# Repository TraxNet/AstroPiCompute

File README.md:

# AstroPiCompute
Astronomy 12V PSU with raspberryPi connection

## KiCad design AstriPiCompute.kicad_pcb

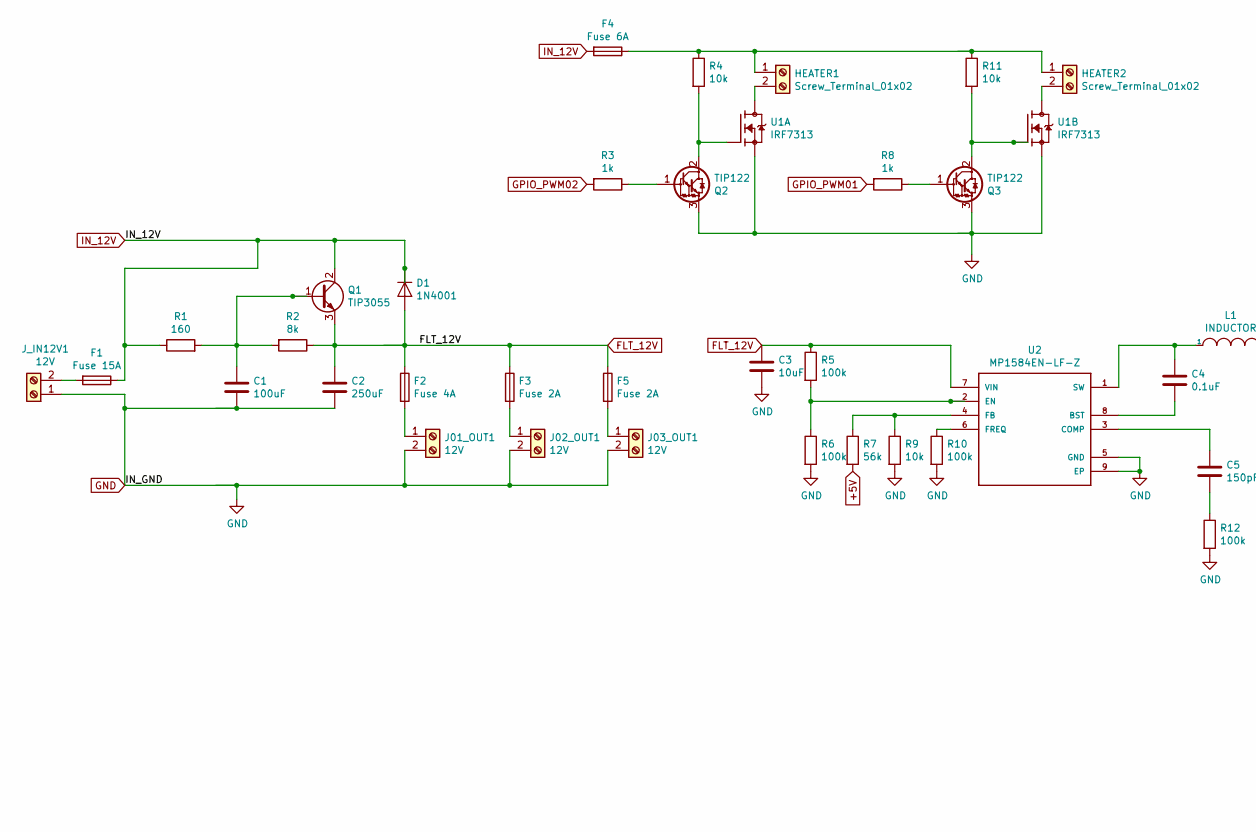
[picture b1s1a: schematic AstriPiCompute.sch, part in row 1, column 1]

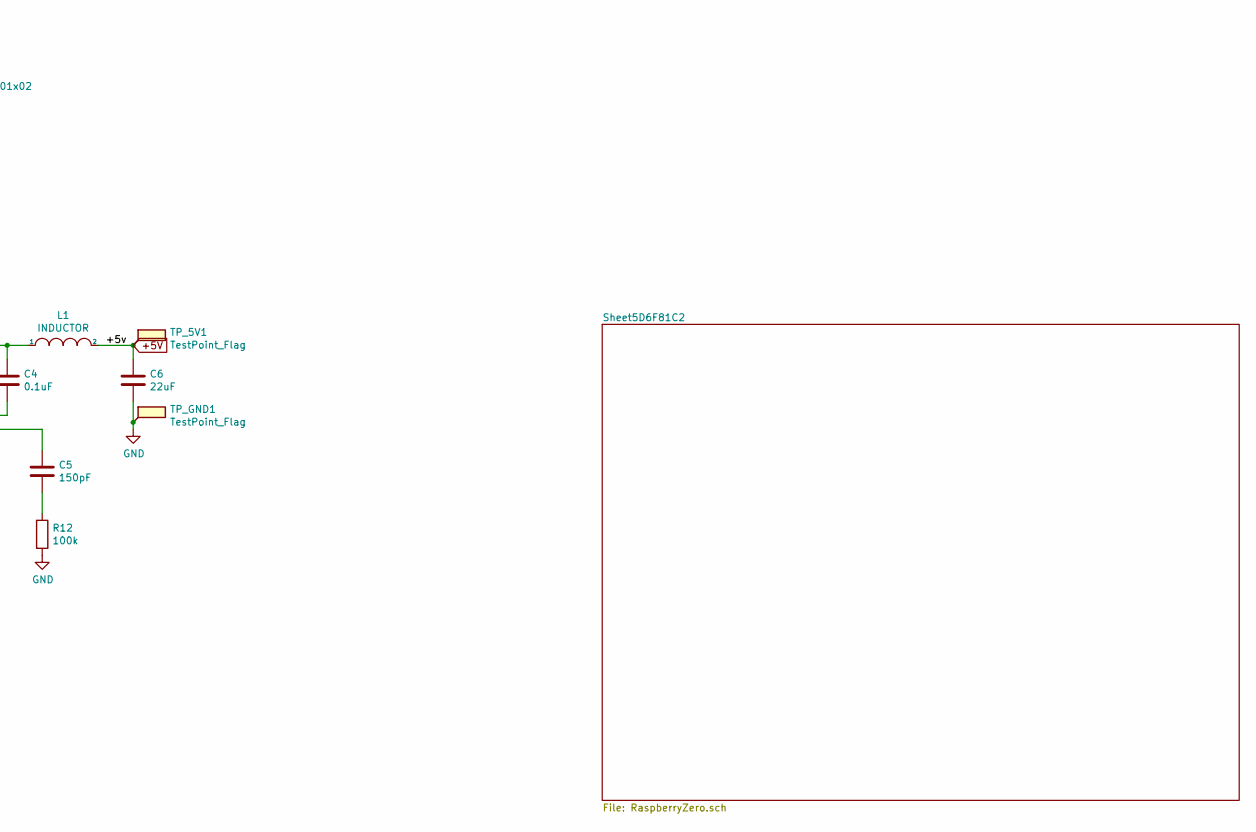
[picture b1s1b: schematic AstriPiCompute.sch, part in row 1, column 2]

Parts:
C1: 100uF; CP_Elec_5x5.4
C2: 250uF; CP_Elec_6.3x5.4
C3: 10uF; C_0805_2012Metric
C4: 0.1uF; C_0805_2012Metric
C5: 150pF; C_0805_2012Metric
C6: 22uF; C_0805_2012Metric
D1: 1N4001; D_0805_2012Metric_Pad1.15x1.40mm_HandSolder
F1: Fuse 15A; Fuse_1206_3216Metric_Pad1.42x1.75mm_HandSolder
F2: Fuse 4A; Fuse_1206_3216Metric_Pad1.42x1.75mm_HandSolder
F3, F5: Fuse 2A; Fuse_1206_3216Metric_Pad1.42x1.75mm_HandSolder
F4: Fuse 6A; Fuse_1206_3216Metric_Pad1.42x1.75mm_HandSolder
HEATER1, HEATER2: Screw_Terminal_01x02; SolderWirePad_1x02_P5.08mm_Drill1.5mm
J01_OUT1, J02_OUT1, J03_OUT1: 12V; SolderWirePad_1x02_P5.08mm_Drill1.5mm
J_IN12V1: 12V; SolderWirePad_1x02_P5.08mm_Drill1.5mm
L1: INDUCTOR; L_Bourns-SRN1060
Q1: TIP3055; TO-218-3_Vertical
Q2, Q3: TIP122; TO-220-3_Vertical
R1: 160; R_0805_2012Metric
R2: 8k; R_0805_2012Metric
R3, R8: 1k; R_0805_2012Metric
R4, R9, R11: 10k; R_0805_2012Metric
R5, R6, R10, R12: 100k; R_0805_2012Metric
R7: 56k; R_0805_2012Metric
TP_5V1: TestPoint_Flag; TestPoint_Pad_1.0x1.0mm
TP_GND1: TestPoint_Flag; TestPoint_Pad_1.0x1.0mm
U1: IRF7313; SO-8
U2: MP1584EN-LF-Z; SOIC127P600X170-9N

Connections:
+5V: C6.1, L1.2, R7.2, TP_5V1.1; also elsewhere on the board
FLT_12V: C2.1, C3.1, D1.2 (A), F2.1, F3.1, F5.1, Q1.3 (E), R2.1, R5.1, U2.7 (VIN)
GND: C1.2, C2.2, C3.2, C6.2, J01_OUT1.2, J02_OUT1.2, J03_OUT1.2, J_IN12V1.1, Q2.3 (E), Q3.3 (E), R6.2, R9.2, R10.2, R12.2, TP_GND1.1, U1.1 (S), U1.3 (S), U2.5 (GND), U2.9 (EP); also elsewhere on the board
GPIO_PWM01: R8.2; also elsewhere on the board
GPIO_PWM02: R3.2; also elsewhere on the board
IN_12V: D1.1 (K), F1.1, F4.2, Q1.2 (C), R1.1
unnamed: C1.1, Q1.1 (B), R1.2, R2.2
unnamed: C4.1, L1.1, U2.1 (SW)
unnamed: C4.2, U2.8 (BST)
unnamed: C5.1, U2.3 (COMP)
unnamed: C5.2, R12.1
unnamed: F1.2, J_IN12V1.2
unnamed: F2.2, J01_OUT1.1
unnamed: F3.2, J02_OUT1.1
unnamed: F4.1, HEATER1.1, HEATER2.1, R4.1, R11.1
unnamed: F5.2, J03_OUT1.1
unnamed: HEATER1.2, U1.7 (D), U1.8 (D)
unnamed: HEATER2.2, U1.5 (D), U1.6 (D)
unnamed: Q2.1 (B), R3.1
unnamed: Q2.2 (C), R4.2, U1.2 (G)
unnamed: Q3.1 (B), R8.1
unnamed: Q3.2 (C), R11.2, U1.4 (G)
unnamed: R5.2, R6.1, U2.2 (EN)
unnamed: R7.1, R9.1, U2.4 (FB)
unnamed: R10.1, U2.6 (FREQ)

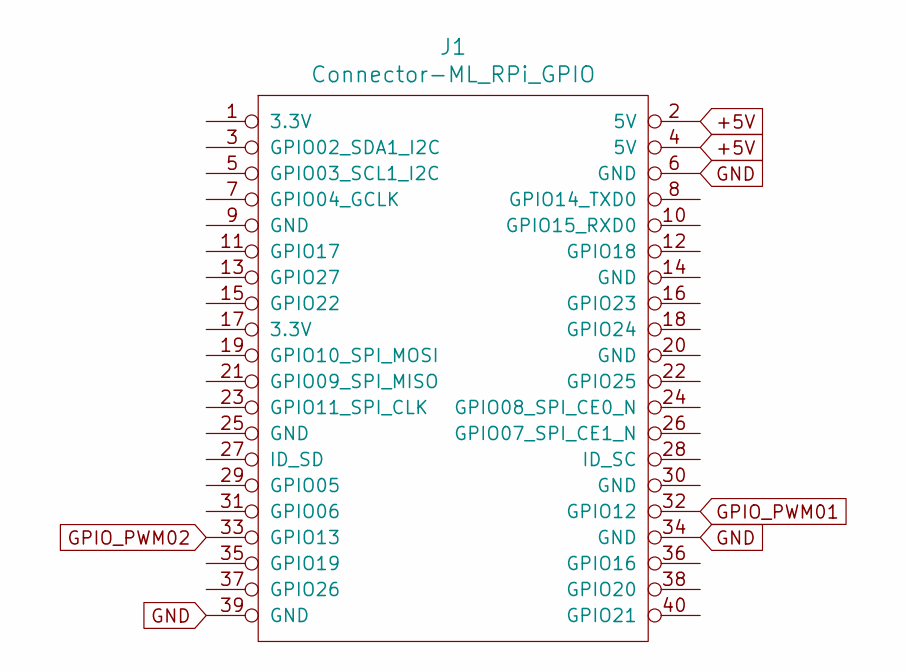
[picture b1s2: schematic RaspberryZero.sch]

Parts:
J1: Connector-ML_RPi_GPIO; PinHeader_2x20_P2.54mm_Vertical

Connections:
+5V: J1.2 (5V), J1.4 (5V); also elsewhere on the board
GND: J1.6 (GND), J1.34 (GND), J1.39 (GND); also elsewhere on the board
GPIO_PWM01: J1.32 (GPIO12); also elsewhere on the board
GPIO_PWM02: J1.33 (GPIO13); also elsewhere on the board

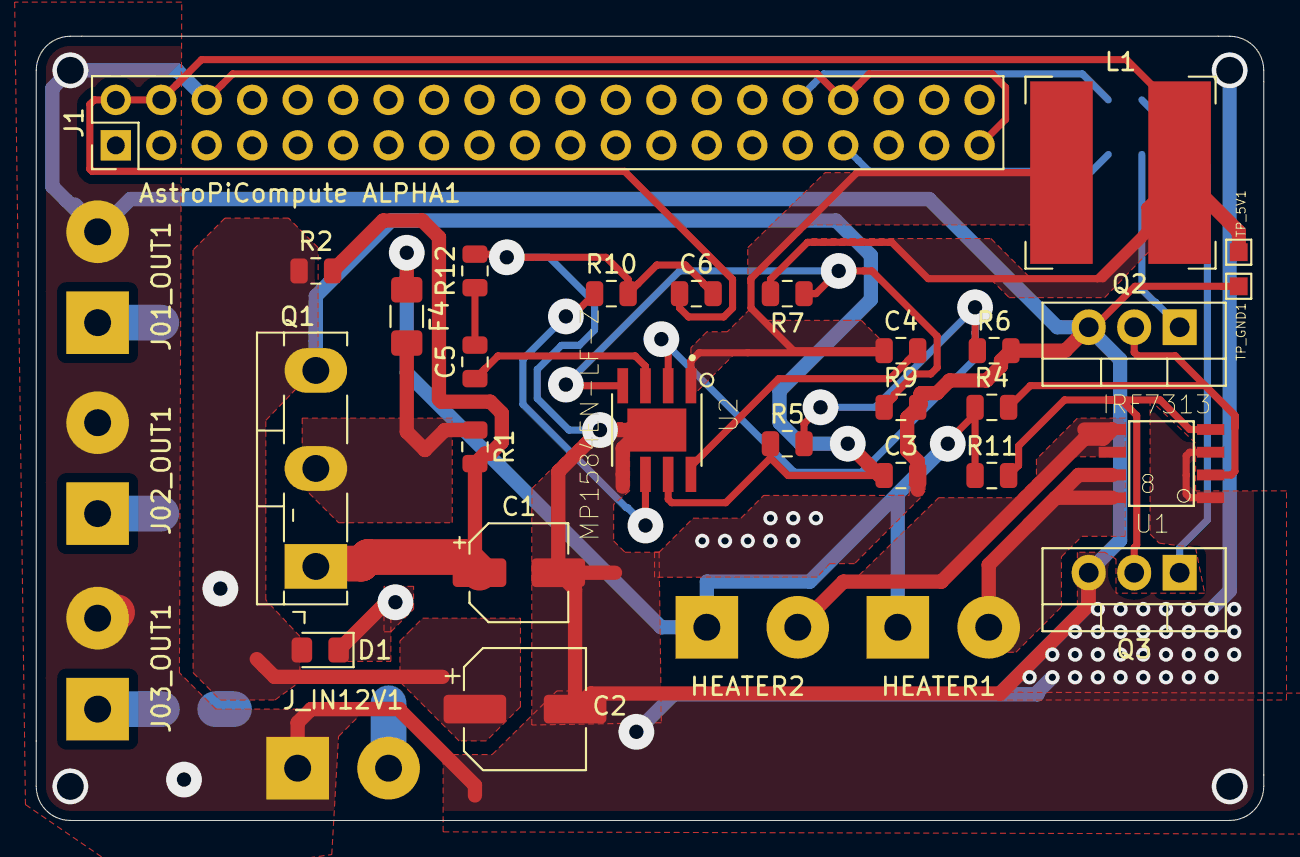
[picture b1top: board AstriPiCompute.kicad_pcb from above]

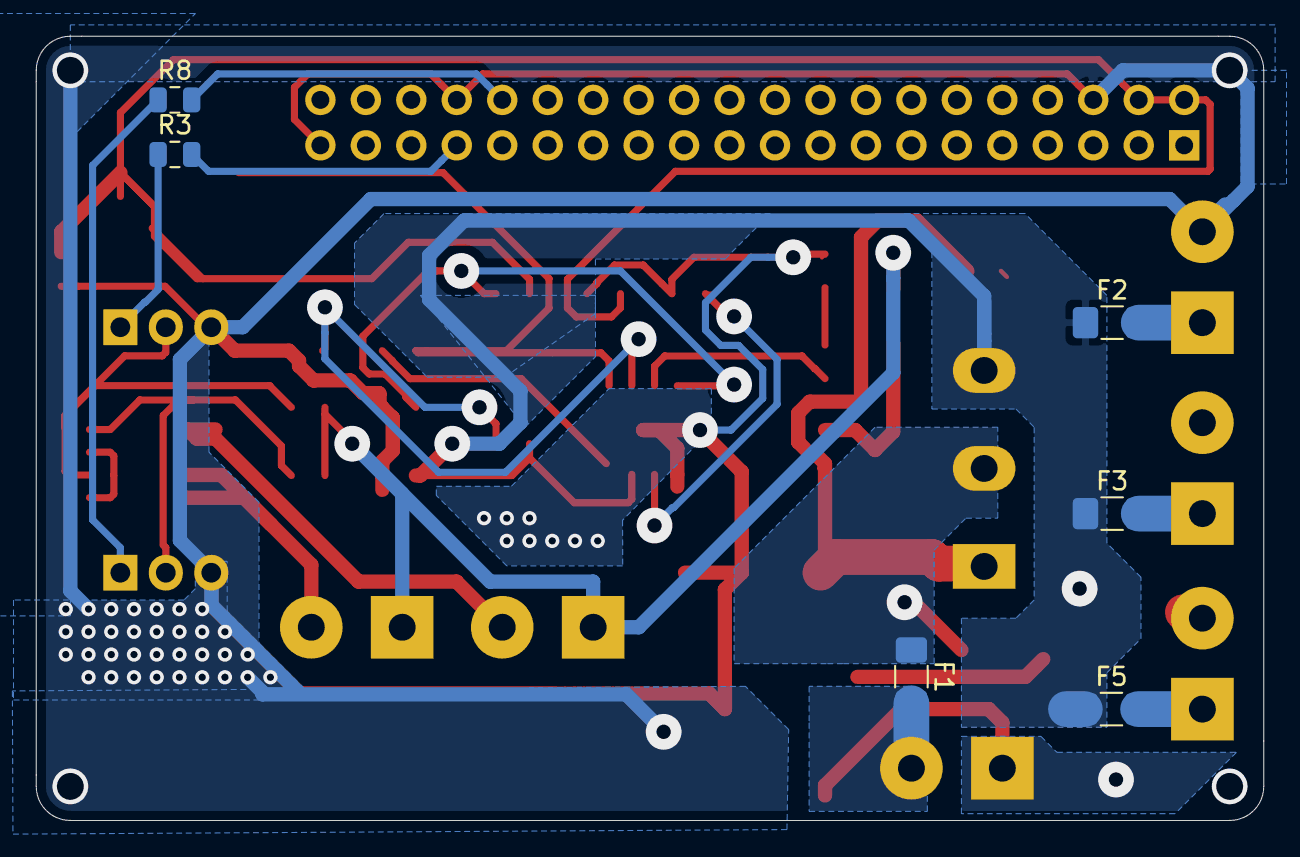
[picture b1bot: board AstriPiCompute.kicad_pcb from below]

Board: 2 copper layers, 68.6 x 43.8 mm, 39 parts (6 on the bottom side), 25 nets.

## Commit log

2020-01-27 Initial Repo Setup
2020-01-27 Layout redesign. More compact footprint PCB
2020-01-27 Exported Gerbers
2020-01-28 Beautify pcb cutout
2020-01-29 Minor changes. Added project mindmap with ideas
2020-01-30 Major PCB changes. Termal releaf areas added
2020-01-30 Revert "Merge remote-tracking branch 'origin/master'"
    This reverts commit 01d5573d911b73708b66d7c6ff1ca1f5e8e3ffb4.
2020-01-31 Reworked 12V connectors for 5mm size
2020-02-01 Fine-tunes for milling w/ The Ant PCB
2020-02-08 flat cam project update for The Ant PCB
2020-04-05 Square PCB for easy milling and testing
